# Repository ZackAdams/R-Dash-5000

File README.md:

R-Dash-5000
===========

Files for making your own R Dash 5000 head.

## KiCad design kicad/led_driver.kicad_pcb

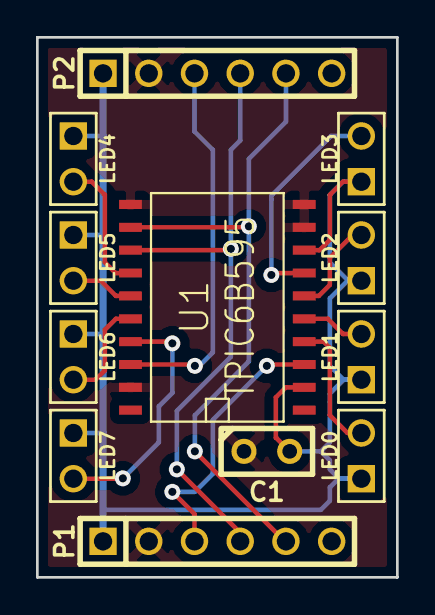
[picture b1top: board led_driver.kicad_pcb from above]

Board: 2 copper layers, 20.0 x 30.0 mm, 12 parts (0 on the bottom side), 14 nets.

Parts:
C1: C; C1
LED0, LED1, LED2, LED3, LED4, LED5, LED6, LED7: LED_1; PIN_ARRAY_2X1
P1, P2: CONN_6; PIN_ARRAY-6X1
U1: TPIC6B595; SO20L

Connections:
/RCK: P1.5, P2.5, U1.12
/SER_IN: P1.3, U1.3
/SER_OUT: P2.3, U1.18
/SRCK: P1.4, P2.4, U1.13
GND: C1.1, P1.2, P2.2, U1.9, U1.10, U1.11, U1.19
unnamed: LED3.2, U1.7
unnamed: LED1.2, U1.5
unnamed: LED2.2, U1.6
unnamed: LED4.2, U1.14
unnamed: LED6.2, U1.16
unnamed: LED7.2, U1.17
unnamed: LED5.2, U1.15
unnamed: LED0.2, U1.4
VCC: C1.2, LED0.1, LED1.1, LED2.1, LED3.1, LED4.1, LED5.1, LED6.1, LED7.1, P1.1, P2.1, U1.2, U1.8

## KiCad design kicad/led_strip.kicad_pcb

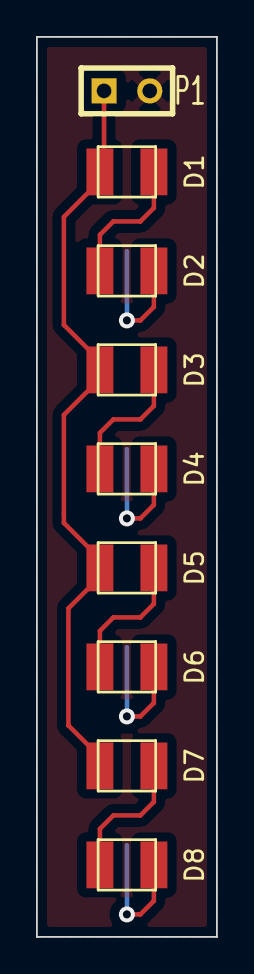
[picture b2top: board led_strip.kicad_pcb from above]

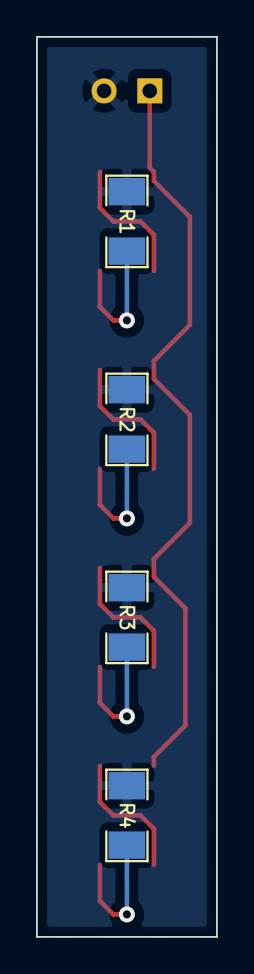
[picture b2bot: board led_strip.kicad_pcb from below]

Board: 2 copper layers, 10.0 x 50.0 mm, 13 parts (4 on the bottom side), 10 nets.

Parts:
D1, D2, D3, D4, D5, D6, D7, D8: LED; LED-PLCC2
P1: CONN_2; SIL-2
R1, R2, R3, R4: R; SM1206

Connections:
GND: P1.2, R1.1, R2.1, R3.1, R4.1
unnamed: D7.2, D8.1
unnamed: D1.2, D2.1
unnamed: D2.2, R1.2
unnamed: D3.2, D4.1
unnamed: D4.2, R2.2
unnamed: D5.2, D6.1
unnamed: D6.2, R3.2
unnamed: D8.2, R4.2
VCC: D1.1, D3.1, D5.1, D7.1, P1.1

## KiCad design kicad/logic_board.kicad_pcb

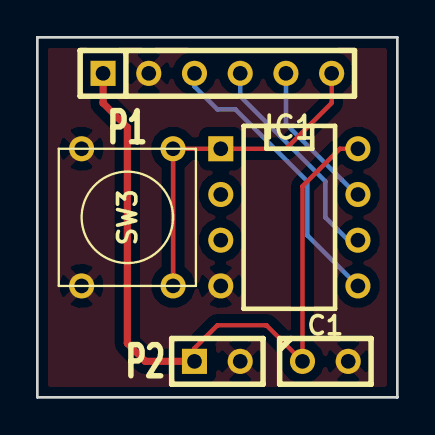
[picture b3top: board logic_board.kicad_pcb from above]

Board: 2 copper layers, 20.0 x 20.0 mm, 5 parts (0 on the bottom side), 6 nets.

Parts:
C1: 10uf; C1
IC1: ATTINY85-P; DIP-8__300
P1: CONN_6; SIL-6
P2: CONN_2; SIL-2
SW3: SW_PUSH; SW_PUSH_SMALL

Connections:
/MISO: IC1.6, P1.4
/MOSI: IC1.5, P1.3
/RESET: IC1.1, P1.6, SW3.2
/SCK: IC1.7, P1.5
GND: C1.2, IC1.4, P1.2, P2.2, SW3.1
VCC: C1.1, IC1.8, P1.1, P2.1

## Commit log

2013-11-27 Initial commit of all project files
